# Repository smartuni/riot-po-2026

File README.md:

# RIOT im Internet of Things, Sommersemester 2026

Welcome to the primary repository of the RIOT im Internet of Things project for the Summer 2026 semester at HAW Hamburg. The project is concerned with designing, implementing and presenting technologies to improve the city of Hamburg's methods of managing its harbor's floodgates.

## The Current Situation

Currently, the methods for ensuring floodgates are closed in the event of a flood are inefficient. Field workers receive orders, send updates and otherwise communicate with the central office via walkie-talkies. The central office relies on pen-and-paper record-keeping to log events, such as gates being opened or closed.

## Our Proposed Solution

The solution proposed and developed by our team is as follows: 

- Floodgates will be fitted with sensors, called "senseGates," which autonomously report the state of the gate (open or closed) to a server located in the central office.
- Field workers will be issued devices, called "senseMates," which receive orders from the central office. senseMates will also record the state of nearby gates by communicating with the senseGates, enabling workers to confirm or refute the state reported by the senseGate.
- The workers at the office will be given a web app with a user interface, allowing them to track the status of gates in real time, as well as providing a digital record of the status of gates and allowing them to issue orders without the need for walkie-talkie communication.

Our proposed solution replaces the inefficient methods currently used by the city of Hamburg with fast and reliable digital methods, saving crucial time in the event of a flood.

## How to start the project

### Nodes

#### Build prerequisities

First, make sure that the riot submodule is downloaded:
```bash
git submodule init
git submodule update
```

To build the firmware, flash, and provision the nodes, the following tools need to be installed
```
make
docker
uv
```

To use a python venv, run the following commands in the root directory of the project:
```bash
uv venv --seed
source .venv/bin/activate
```
>Note: some Linux distributions no longer allow installing python packages via pip directly. It is recommended to use a venv instead for easier package management.

#### Building firmware

Navigate to the respective folders for senseMate or senseGate in `nodes/firmware/applications/sense{Mate|Gate}`

> Note: To build the firmware for the previous (v1) hardware revision, instead run:
> ```bash
> BOARD=adafruit-feather-nrf52840-sense make all -j
> ```

Set environment variable to use the docker build stack:
```bash
export BUILD_IN_DOCKER=1
```

Build the firmware using 
```bash
make all -j
```
>Note: when building for the first time, the entire build toolchain will be set up in the docker container automatically. This will take some time and download several GB of data. Make sure to have at least 20 GB of storage available for this.

#### Flashing firmware

To flash, make sure to install the following python dependencies using `pip install` (ideally in the uv venv set up ealier):
- pyserial
- psutil

Make sure that the user account doing the flashing has the necessary permission, e.g. being in the `dialout` group on linux or similar for other operating systems.

Flash the previously built firmware using
```bash
make flash
```

If no identity is provisioned on the external flash (like after inital flashing of a new board), the screen of a senseMate will stay blank after successfully flashing and no (or not much) log output will appear.

#### Provisioning devices

Provisioning of devices is done via the identity-manager module found at `/nodes/firmware/identity-manager/`

> Note: uv must be installed to run the identity manager.

##### Setup

> Note: A high level overview of node identities and identity gossipping can be found in [Node Identity and Identity Gossipping](./nodes/node_identity_and_identity_gossipping.md).

To use the credential manager, it needs to be set up.
First, create the config for the credential manager at `nodes/firmware/identity-manager/config.yaml`. See the example config (`config.examle.yaml`) for reference.

Now, log in to the [TTN Console](https://eu1.cloud.thethings.network) and navigate to Applications → your application → API keys, create a new API key, and put it into the config. Update your application ID if necessary. 

Next, either import an existing root identity into `nodes/firmware/identity-manager/identities/root`, or create a new one using the identity manager as follows:

```bash
./identity-manager.py root create
```
>Note: the same root identity must be used for all nodes for them to be able to communicate with each other successfully.

Next, individual node identities need to be configured. These can either be imported by putting their respective ID info files into `nodes/firmware/identity-manager/identities/node/` or by creating them using the identity manager as follows:

```bash
./identity-manager.py node create [senseMate|senseGate] [-i 1]
```
This command creates a new identity for either a senseMate or a senseGate with the ID 1.
The ID parameter (`-i [id]`) is optional and can be omitted, in that case the next free ID gets chosen

###### Provisioning

When provisioning a node, it is best practice to wipe the external storage, so a subsequent flash is going to succeed without issues.
This is done by running:
```bash
./identity-manager.py node wipe
```

Now the node can be provisioned with the previously generated identity:
```bash
./identity-manager.py node provision [senseMate|senseGate] ID
```

>Warning: The wipe and provision commands try to communicate with the node via `/dev/ttyACM0`. Make sure to only have one node connected at a time to avoid confusion. If the communication fails, check if another device is already registered.

>Note: Once a node is provisioned, flashing a new firmware on it does not affect the identity as it is stored on the flash. This provisioning step only needs to be done once (unless the identity gets deleted from the flash somehow).

More info can be found in the [README of the identity-manager module](nodes/firmware/identity-manager/README.md).

### Dashboard

Required dependencies

- docker

#### MQTT connection setup

to obtain MQTT credentials for the connection to the things network, log into the [TTN Console](https://eu1.cloud.thethings.network)

Navigate to Applications → your application → other integrations → MQTT
Generate a new API key here, and insert the following into `server/backend/src/main/resources/application.yml`:

```
mqtt:
  broker: ssl://eu1.cloud.thethings.network:8883
  clientId: testing ← this does not matter
  username: hawriotfloodgates@ttn ← you find this on the mqtt page
  applicationId: hawriotfloodgates ← your application ID
  password: NNSXS.XXXXXXXXXX.XXXXXXX ← the API key goes here
  subscribeTopic: v3/hawriotfloodgates@ttn/devices/+/up  ← put the username in here
```

>Hint: when starting the backend container, look for the following lines in the output:
>
>```
>MQTT Publisher verbunden
>MQTT-Client gestartet, warte auf Nachrichten...
>```
>If these don't appear, double check your configuration and make sure that the MQTT broker is reachable via the network. As of summer 2026, port 8883 is blocked in the HAW network, so use a VPN or mobile hotspot if necessary. 

#### Starting the Dashboard

Start the containers with `docker compose up`

>Note: when testing out new changes to the code, make sure to delete the built container images using `docker image rm <image>` before running them again to get the latest state.

After full startup, the dashboard is reachable via the browser at http://localhost:3000

To stop the containers, use `docker compose down`.
To stop and delete the volumes with the database state, use `docker compose down -v`.

## Notes for future reference:
Notes from the summer 2026 project group to future contributors.

The working state presented at the summer 2026 presentation can be found at the git tag `presentation-summer-2026`

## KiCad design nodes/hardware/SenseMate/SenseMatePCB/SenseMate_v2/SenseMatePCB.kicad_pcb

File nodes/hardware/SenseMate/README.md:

# Description

This is the SenseMate hardware directory of the hardware directory. 

# Overview

The SenseMate directory includes modules to control the peripherals listed below.

## Modules

- Sound module
- Display module
- Vibration Module

## Requirements

Additionally to the Nordic nRF52840 board, the following peripherals are required for the full utilization of the project:

- Power Switch​
- Battery​
- Thumbwheel​
- Navigation​
- Display​
- Soundbuzzer​
- Vibrationmotor​

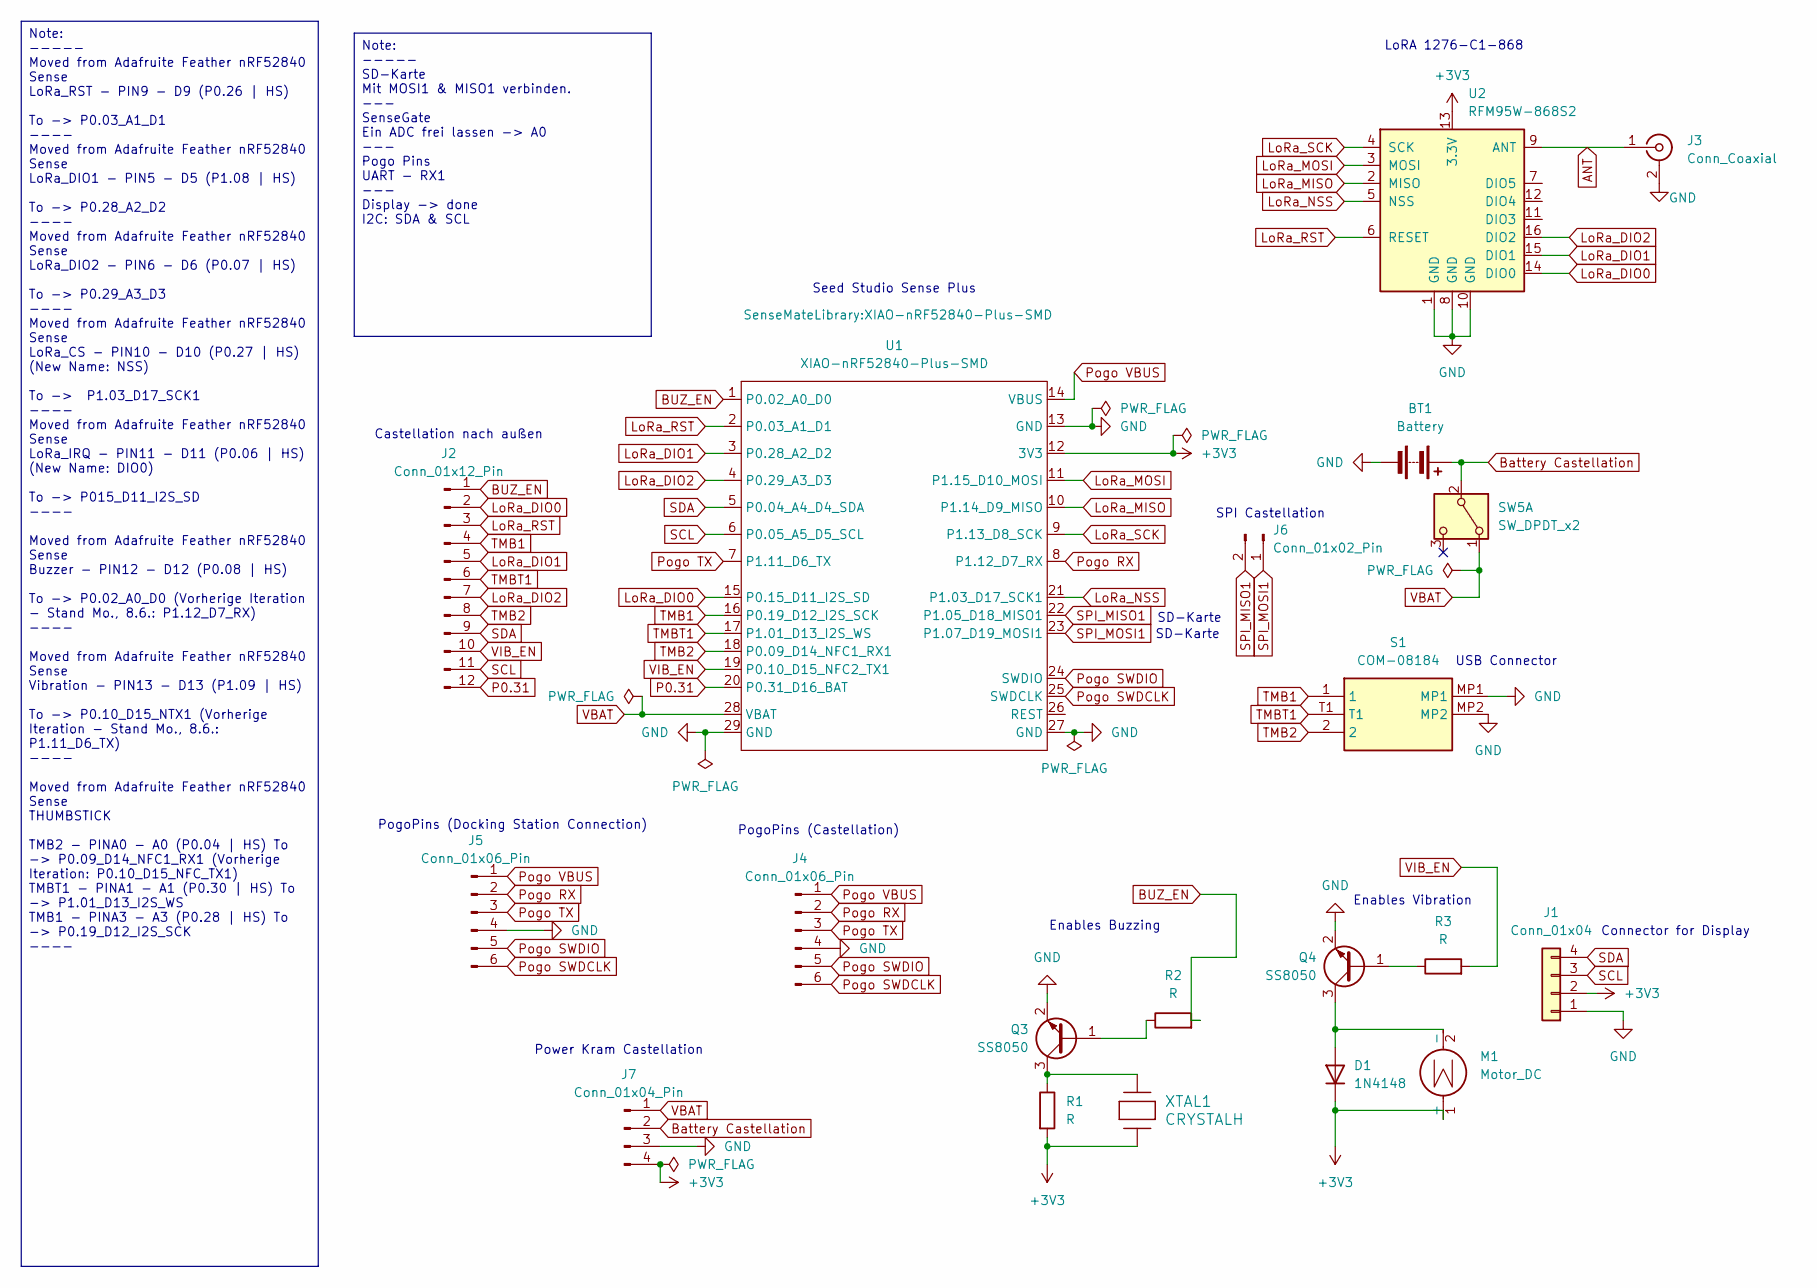
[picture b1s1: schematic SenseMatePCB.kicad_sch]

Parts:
BT1: Battery; JST_PH_S2B-PH-K_1x02_P2.00mm_Horizontal
D1: 1N4148; D_SOD-323
J1: Conn_01x04; PinHeader_1x04_P2.54mm_Vertical
J2: Conn_01x12_Pin; Castellated_1x12_2.00mm
J3: Conn_Coaxial; U.FL_Molex_MCRF_73412-0110_Vertical
J4: Conn_01x06_Pin; Castellated_1x6_2.00mm
J5: Conn_01x06_Pin; PinHeader_1x06_P2.54mm_Vertical
J6: Conn_01x02_Pin; Castellated_1x2_2.00mm
J7: Conn_01x04_Pin; Castellated_1x4_2.00mm
M1: Motor_DC; PinHeader_1x02_P2.54mm_Vertical
Q3, Q4: SS8050; SOT-23
R1, R2, R3: R; R_0805_2012Metric
S1: COM-08184; COM08184; Manufacturer_Part_Number COM-08184
SW5: SW_DPDT_x2; OS102011MA1QN1
U1: XIAO-nRF52840-Plus-SMD
U2: RFM95W-868S2; HOPERF_RFM9XW_SMD
XTAL1: CRYSTALH; PS1240P02BT

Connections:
+3V3: D1.1 (K), J1.2, J7.4, M1.1 (+), R1.2, U1.12 (3V3), U2.13 (3.3V), XTAL1.1
ANT: J3.1 (In), U2.9 (ANT)
BUZ_EN: J2.1, R2.2, U1.1 (P0.02_A0_D0)
Battery Castellation: BT1.1 (+), J7.2, SW5.2 (B)
GND: BT1.2 (-), J1.1, J3.2 (Ext), J4.4, J5.4, J7.3, Q3.2 (E), Q4.2 (E), S1.MP1, S1.MP2, U1.13 (GND), U1.27 (GND), U1.29 (GND), U2.1 (GND), U2.8 (GND), U2.10 (GND)
LoRa_DIO0: J2.2, U1.15 (P0.15_D11_I2S_SD), U2.14 (DIO0)
LoRa_DIO1: J2.5, U1.3 (P0.28_A2_D2), U2.15 (DIO1)
LoRa_DIO2: J2.7, U1.4 (P0.29_A3_D3), U2.16 (DIO2)
LoRa_MISO: U1.10 (P1.14_D9_MISO), U2.2 (MISO)
LoRa_MOSI: U1.11 (P1.15_D10_MOSI), U2.3 (MOSI)
LoRa_NSS: U1.21 (P1.03_D17_SCK1), U2.5 (NSS)
LoRa_RST: J2.3, U1.2 (P0.03_A1_D1), U2.6 (RESET)
LoRa_SCK: U1.9 (P1.13_D8_SCK), U2.4 (SCK)
unnamed: D1.2 (A), M1.2 (-), Q4.3 (C)
unnamed: Q3.1 (B), R2.1
unnamed: Q3.3 (C), R1.1, XTAL1.2
unnamed: Q4.1 (B), R3.1
P0.31: J2.12, U1.20 (P0.31_D16_BAT)
Pogo RX: J4.2, J5.2, U1.8 (P1.12_D7_RX)
Pogo SWDCLK: J4.6, J5.6, U1.25 (SWDCLK)
Pogo SWDIO: J4.5, J5.5, U1.24 (SWDIO)
Pogo TX: J4.3, J5.3, U1.7 (P1.11_D6_TX)
Pogo VBUS: J4.1, J5.1, U1.14 (VBUS)
SCL: J1.3, J2.11, U1.6 (P0.05_A5_D5_SCL)
SDA: J1.4, J2.9, U1.5 (P0.04_A4_D4_SDA)
SPI_MISO1: J6.2, U1.22 (P1.05_D18_MISO1)
SPI_MOSI1: J6.1, U1.23 (P1.07_D19_MOSI1)
TMB1: J2.4, S1.1, U1.16 (P0.19_D12_I2S_SCK)
TMB2: J2.8, S1.2, U1.18 (P0.09_D14_NFC1_RX1)
TMBT1: J2.6, S1.T1, U1.17 (P1.01_D13_I2S_WS)
VBAT: J7.1, SW5.1 (A), U1.28 (VBAT)
VIB_EN: J2.10, R3.2, U1.19 (P0.10_D15_NFC2_TX1)

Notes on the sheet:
PogoPins (Docking Station Connection)
Seed Studio Sense Plus
SPI Castellation
USB Connector
SD-Karte
Castellation nach außen
Power Kram Castellation
Enables Vibration
LoRA 1276-C1-868
PogoPins (Castellation)
Connector for Display
Enables Buzzing
Note: ----- Moved from Adafruite Feather nRF52840 Sense LoRa_RST - PIN9 - D9 (P0.26 | HS) To -> P0.03_A1_D1 ---- Moved from Adafruite Feather nRF52840 Sense LoRa_DIO1 - PIN5 - D5 (P1.08 | HS) To -> P0.28_A2_D2 ---- Moved from Adafruite Feather nRF52840 Sense LoRa_DIO2 - PIN6 - D6 (P0.07 | HS) To ->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
Note: ----- SD-Karte Mit MOSI1 & MISO1 verbinden. --- SenseGate Ein ADC frei lassen -> A0 --- Pogo Pins UART - RX1 --- Display -> done I2C: SDA & SCL

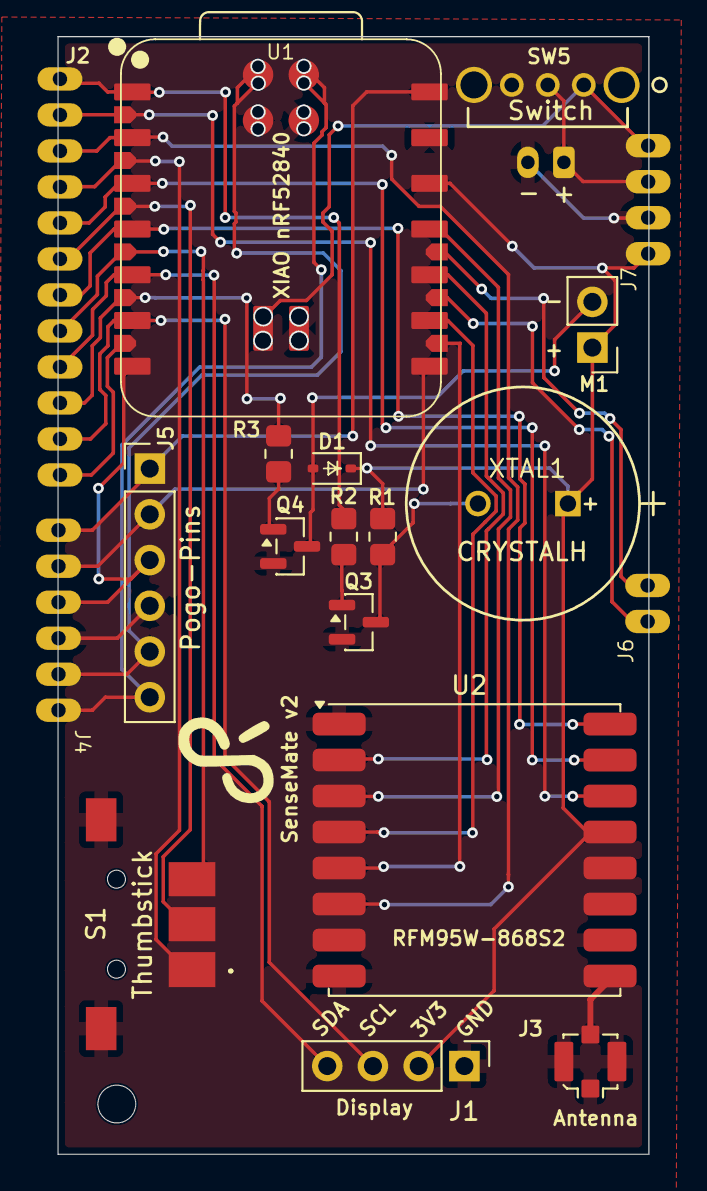
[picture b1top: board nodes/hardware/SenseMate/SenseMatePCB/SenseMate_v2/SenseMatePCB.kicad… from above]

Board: 4 copper layers, 32.8 x 62.1 mm, 20 parts (1 on the bottom side), 32 nets.

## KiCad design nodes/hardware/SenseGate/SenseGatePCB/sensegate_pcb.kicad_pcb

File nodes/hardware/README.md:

# Description

This is the hardware directory of the nodes directory.

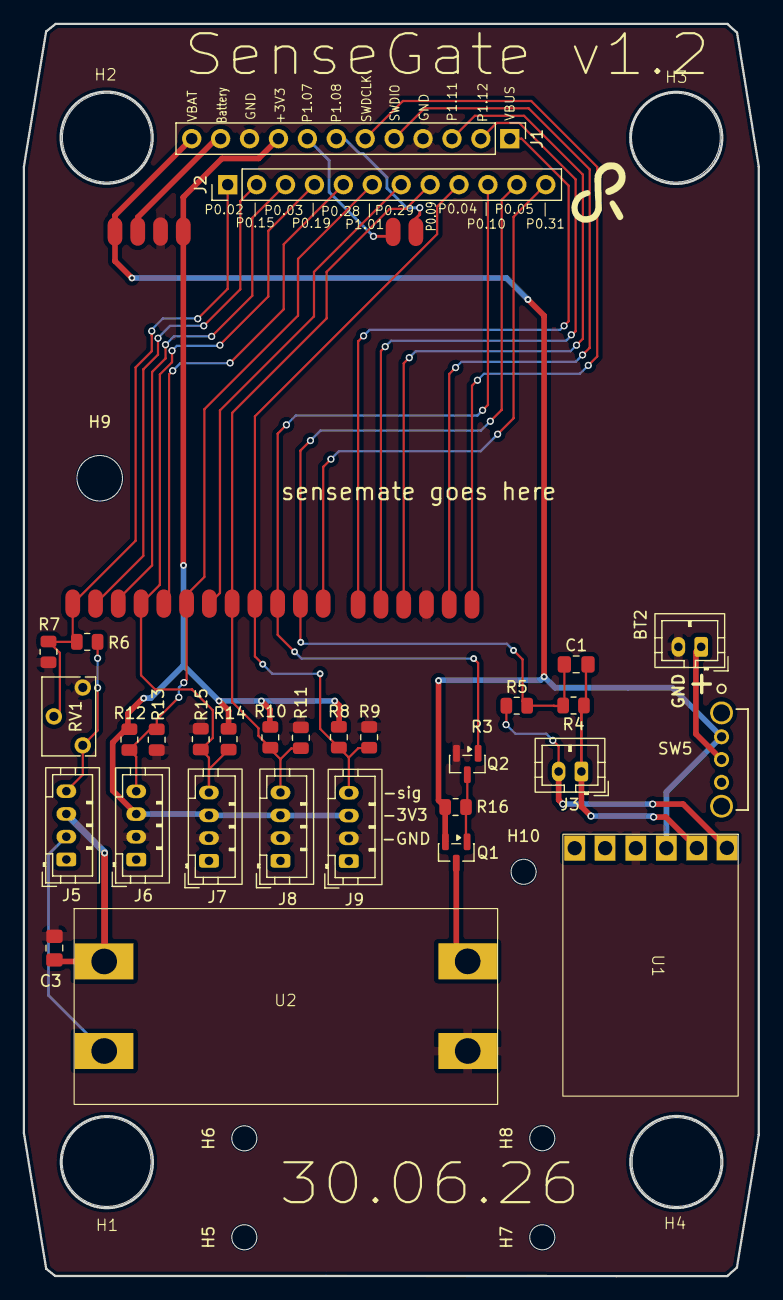
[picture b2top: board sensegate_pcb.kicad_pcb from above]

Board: 2 copper layers, 64.6 x 110.0 mm, 41 parts (0 on the bottom side), 31 nets.

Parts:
BT2: Battery; JST_PH_B2B-PH-K_1x02_P2.00mm_Vertical
C1, C3: C; C_0805_2012Metric_Pad1.18x1.45mm_HandSolder
H1, H2, H3, H4: MountingHole; mounting_hole_7.8mm
H5, H6, H7, H8, H10: MountingHole; MountingHole_2.2mm_M2
H9: MountingHole; MountingHole_4mm
J1, J2: Conn_01x12_Pin; PinHeader_1x12_P2.54mm_Vertical
J3: Conn_01x02_Socket; JST_PH_B2B-PH-K_1x02_P2.00mm_Vertical
J4: Conn_01x24_Pin; SenseMateInterface
J5, J6, J7, J8, J9: Conn_01x04_Socket; JST_PH_B4B-PH-K_1x04_P2.00mm_Vertical
Q1: AO3401A; SOT-23
Q2: BSS138; SOT-23
R4, R5, R6, R7, R8, R9, R10, R11, R12, R13, R14, R15, R16: R; R_0805_2012Metric
RV1: R_Potentiometer; Potentiometer_Bourns_3266W_Vertical
SW5: SW_DPDT_x2; OS102011MA1QN1
U1: DD05CVSA
U2: mt3608_dcdc_converter; MT3608_solarbotics

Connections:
20V: C3.2, J5.3, U2.1 (VOUT+)
+3V3: J1.9, J4.+3V3 (Pin_21), J6.3, J7.3, J8.3, J9.3, R8.1, R10.1, R12.1, R14.1
GND: BT2.2 (-), C3.1, J1.4, J1.10, J4.GND (Pin_16), J6.2, J7.2, J8.2, J9.2, Q2.2 (S), R7.1, R9.2, R11.2, R13.2, R15.2, RV1.3, U1.4 (GND(bat-)), U2.4 (VIN-)
GND_IS: J5.2, U2.2 (VOUT-)
IS_ADC: J2.1, J4.P0.02_A0_D0_/_BUZ_EN (Pin_1), R6.1, R7.2, RV1.2
MON_SOLAR: C1.1, J2.11, J4.P0.05_A5_D5_/_SCL (Pin_11), R4.2, R5.2
unnamed: BT2.1 (+), SW5.2 (B)
unnamed: J1.1, J4.VBUS_/_pogo_vbus (Pin_13)
unnamed: J1.2, J4.P1.12_D7_/_pogo_rx (Pin_14)
unnamed: J1.3, J4.P1.11_D6_/_pogo_tx (Pin_15)
unnamed: J1.5, J4.SWDIO_/_pogo_swdio (Pin_17)
unnamed: J1.6, J4.SWDCLK_/_pogo_swdclk (Pin_18)
unnamed: J1.7, J4.P1.05_D18_/_spi_mis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 (Pin_19)
unnamed: J1.8, J4.P1.07_D19_/_spi_mos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 (Pin_20)
unnamed: J1.11, J4.Battery (Pin_23)
unnamed: J2.2, J4.P0.15_D11_/_lora_di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 (Pin_2)
unnamed: J2.3, J4.P0.03_A1_D1_/_lora_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 (Pin_3)
unnamed: J2.5, J4.P0.28_A2_D2_/_lora_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 (Pin_5)
unnamed: J2.7, J4.P0.29_A3_D3_/_lora_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 (Pin_7)
unnamed: J2.12, J4.P0.31_D16 (Pin_12)
unnamed: C1.2, J3.1, R4.1, U1.2 (GND)
unnamed: J3.2, R5.1, U1.1 (VIN)
unnamed: J5.4, R6.2, RV1.1
unnamed: Q1.3 (D), U2.3 (VIN+)
unnamed: Q1.1 (G), Q2.3 (D), R16.1
TOG_20V: J2.10, J4.P0.10_D15_/_VIB_EN (Pin_10), Q2.1 (G)
VBAT: J1.12, J4.VBAT (Pin_24), Q1.2 (S), R16.2, SW5.1 (A), U1.3 (Bat+)
reed_sw_01_measure: J2.8, J4.P0.09_D14_/_TMB2 (Pin_8), J8.4, R10.2, R11.1
reed_sw_02_measure: J2.6, J4.P1.01_D13_/_TMBT1 (Pin_6), J6.4, R12.2, R13.1
reed_sw_03_measure: J2.4, J4.P0.19_D12_/_TMB1 (Pin_4), J7.4, R14.2, R15.1
reed_sw_04_measure: J2.9, J4.P0.04_A4_D4_/_SDA (9), J9.4, R8.2, R9.1

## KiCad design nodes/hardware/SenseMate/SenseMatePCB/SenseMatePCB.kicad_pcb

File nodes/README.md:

# Description

This is the node directory of the project. It contains all necessary modules and functions of the SenseMate and SenseGate node.

# Overview

## Custom Modules

custom-modules takes from the available RIOT modules and adapts these to suit the SenseMate project's needs.

These include:
- COSE for CBOR signing
- KEY-DISTRO for secure data signing and verification
- BLE for node-to-node communication via Bluetooth
- LORAWAN for server-to-node and node-to-server communication via LoRaWan
- TABLES to manage state tables and encode them to and decode them from CBOR

## Hardware

SenseMate hardware components and drawings 

## Firmware

SenseMate and SenseGate source code

## Node Identity and Identity Gossipping

A high-level overview of how node identities and identity gossipping work, can be found in [Node Identity and Identity Gossipping](./node_identity_and_identity_gossipping.md).

### Deployment

`make all flash` or with terminal output `make all flash term` TODO

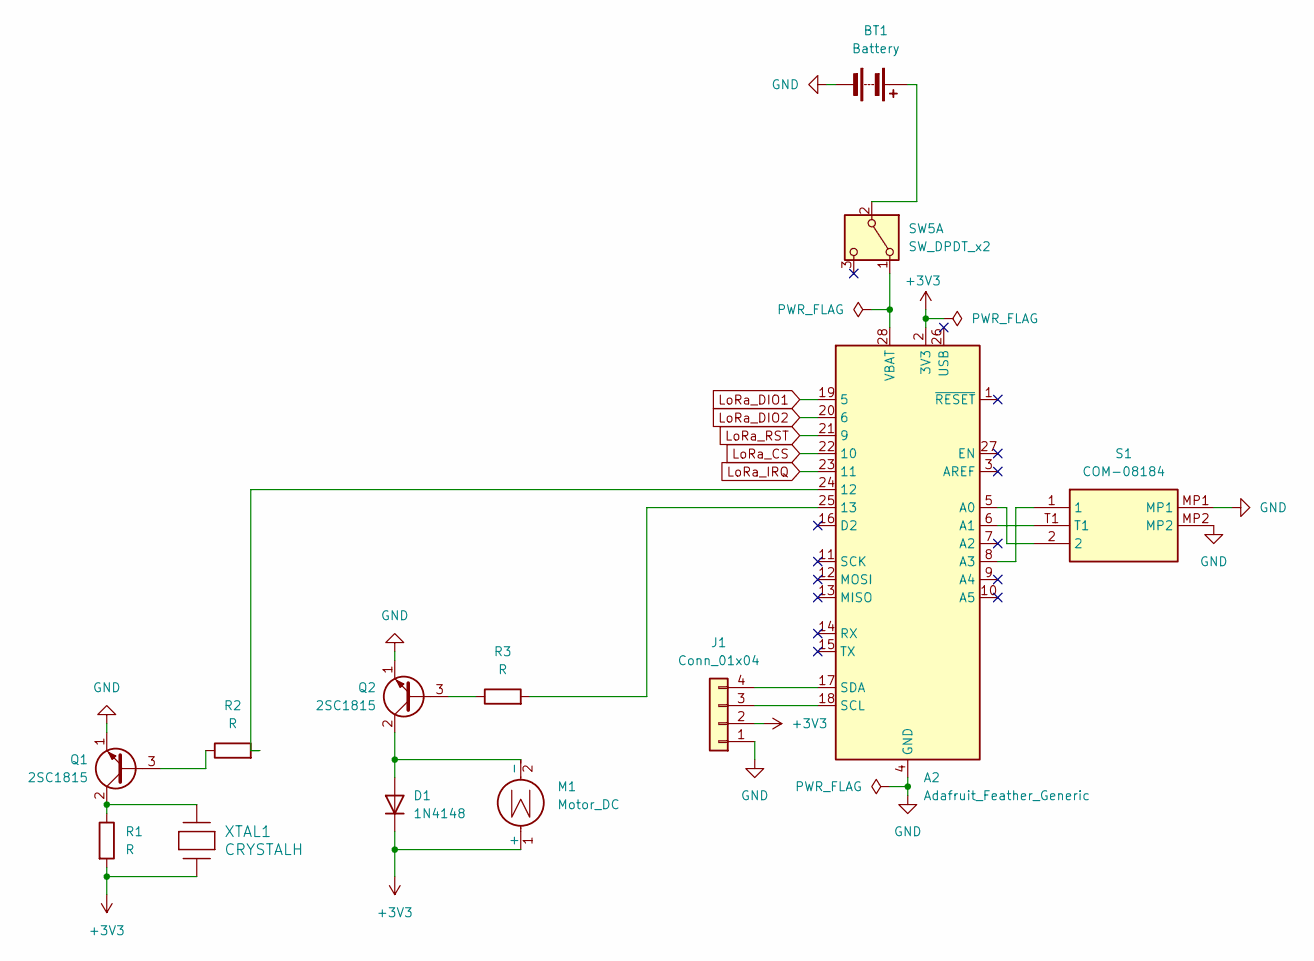
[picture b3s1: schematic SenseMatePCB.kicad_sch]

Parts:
A2: Adafruit_Feather_Generic; Adafruit_Feather_Sense
BT1: Battery; JST_PH_S2B-PH-K_1x02_P2.00mm_Horizontal
D1: 1N4148; D_SOD-323
J1: Conn_01x04; PinHeader_1x04_P2.54mm_Vertical
M1: Motor_DC; PinHeader_1x02_P2.54mm_Vertical
Q1, Q2: 2SC1815; SOT-23
R1, R2, R3: R; R_0805_2012Metric
S1: COM-08184; COM08184; Manufacturer_Part_Number COM-08184
SW5: SW_DPDT_x2; OS102011MA1QN1
XTAL1: CRYSTALH; XTAL_PS1240P02BT_TDK

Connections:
+3V3: A2.2 (3V3), D1.1 (K), J1.2, M1.1 (+), R1.2, XTAL1.1
GND: A2.4 (GND), BT1.2 (-), J1.1, Q1.1 (E), Q2.1 (E), S1.MP1, S1.MP2
LoRa_CS: A2.22 (10)
LoRa_DIO1: A2.19 (5)
LoRa_DIO2: A2.20 (6)
LoRa_IRQ: A2.23 (11)
LoRa_RST: A2.21 (9)
unnamed: A2.24 (12), R2.2
unnamed: A2.25 (13), R3.2
unnamed: A2.5 (A0), S1.2
unnamed: A2.6 (A1), S1.T1
unnamed: A2.8 (A3), S1.1
unnamed: A2.18 (SCL), J1.3
unnamed: A2.17 (SDA), J1.4
unnamed: A2.28 (VBAT), SW5.1 (A)
unnamed: BT1.1 (+), SW5.2 (B)
unnamed: D1.2 (A), M1.2 (-), Q2.2 (C)
unnamed: Q1.3 (B), R2.1
unnamed: Q1.2 (C), R1.1, XTAL1.2
unnamed: Q2.3 (B), R3.1

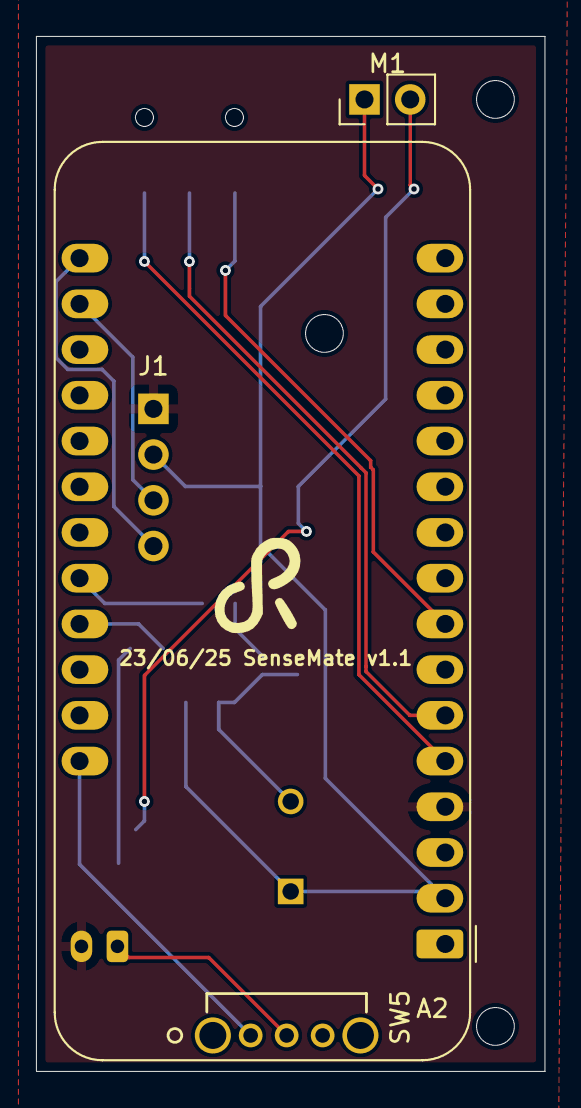
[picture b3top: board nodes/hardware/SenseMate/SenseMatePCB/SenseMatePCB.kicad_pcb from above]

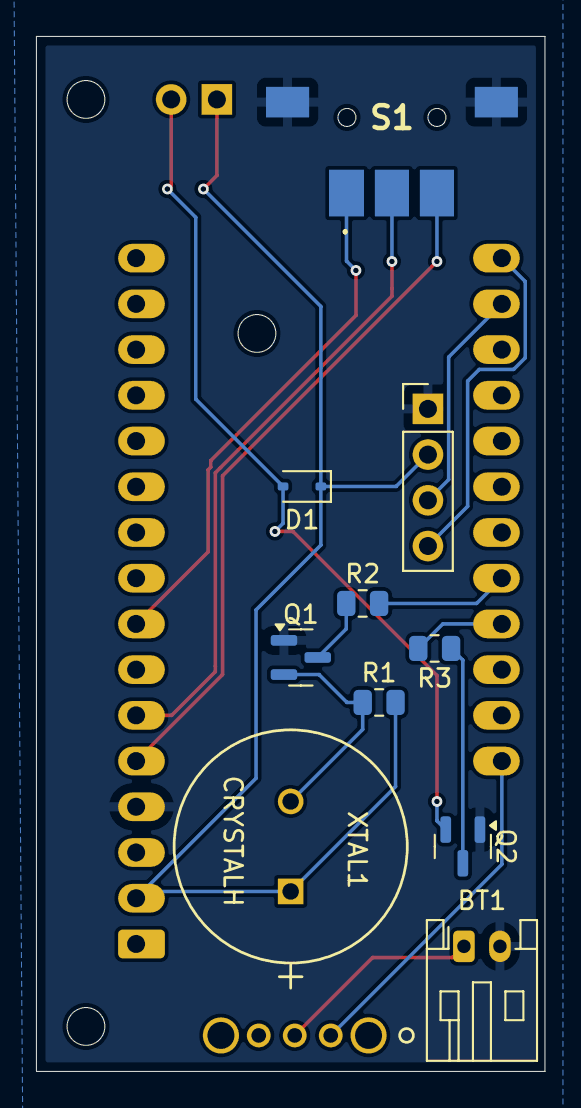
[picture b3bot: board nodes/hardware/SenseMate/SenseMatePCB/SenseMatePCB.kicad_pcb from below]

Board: 2 copper layers, 28.2 x 57.5 mm, 13 parts (10 on the bottom side), 15 nets.

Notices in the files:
parts and their libraries:
Copyright 2016 Accelerated Designs. All rights reserved.
